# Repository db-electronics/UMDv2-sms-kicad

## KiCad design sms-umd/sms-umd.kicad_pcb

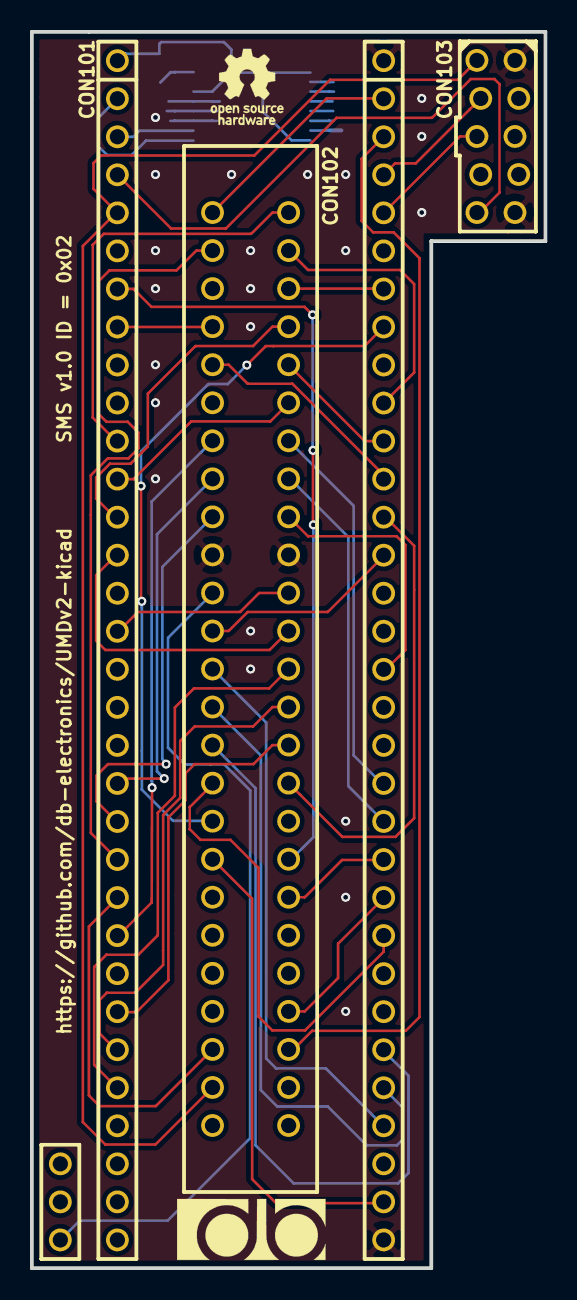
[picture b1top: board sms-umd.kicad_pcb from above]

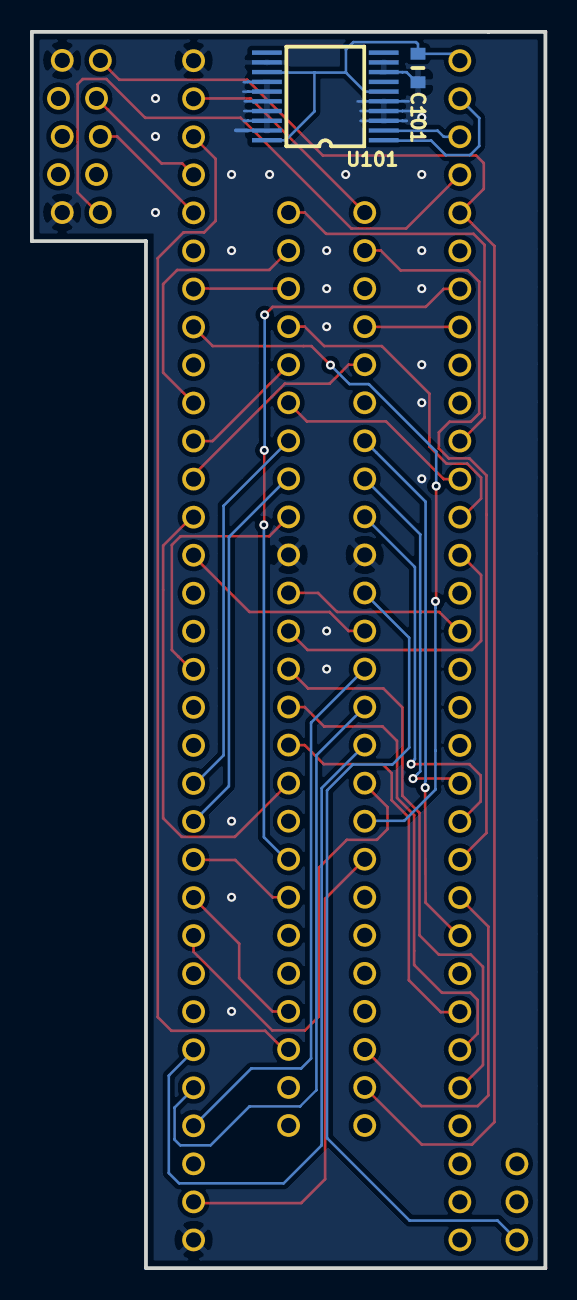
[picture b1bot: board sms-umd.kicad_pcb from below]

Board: 2 copper layers, 34.3 x 82.5 mm, 5 parts (2 on the bottom side), 43 nets.

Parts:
C101: 0.1uF/50V; 0603
CON101: UMDv2-CONN; UMD-CONN-DIP64
CON102: SMS-CONN
CON103: JTAG-2X5-HDR; HDR2X5-JTAG
U101: MCP23008T-E_SS; SSOP-20

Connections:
+3V3: C101.1, CON101.1, U101.6, U101.13, U101.20
/5V_0: CON101.63, CON102.1
/5V_1: CON101.34, CON102.35
/A0: CON101.36, CON102.25
/A1: CON101.28, CON102.26
/A2: CON101.37, CON102.27
/A3: CON101.27, CON102.28
/A4: CON101.38, CON102.29
/A5: CON101.26, CON102.30
/A6: CON101.41, CON102.31
/A7: CON101.52, CON102.32
/A8: CON101.13, CON102.8
/A9: CON101.53, CON102.9
/A10: CON101.12, CON102.12
/A11: CON101.54, CON102.10
/A12: CON101.57, CON102.33
/A13: CON101.8, CON102.7
/A14: CON101.58, CON102.6
/A15: CON101.7, CON102.36
/D0: CON101.14, CON102.24
/D1: CON101.51, CON102.23
/D2: CON101.16, CON102.22
/D3: CON101.48, CON102.18
/D4: CON101.21, CON102.17
/D5: CON101.44, CON102.16
/D6: CON101.20, CON102.15
/D7: CON101.45, CON102.14
/SCL: CON101.2, U101.1
/SDA: CON101.3, U101.2
/TCK: CON101.5, CON102.47, CON103.1
/TDI: CON101.4, CON103.9
/TDO: CON101.61, CON103.3
/TMS: CON101.60, CON103.5
/~BUSACK~: CON101.23, CON102.45
/~BUSREQ~: CON101.42, CON102.44
/~CART~: CON101.67, CON102.21
/~CE~: CON101.24, CON102.13
/~IORQ~: CON101.43, CON102.38
/~MREQ~: CON101.22, CON102.3
/~RD~: CON101.55, CON102.4
/~RST~: CON101.62, CON102.46
/~WR~: CON101.11, CON102.2
GND: C101.2, CON101.33, CON101.64, CON102.19, CON102.20, CON103.2, CON103.10, U101.3, U101.4, U101.5, U101.8, U101.9, U101.12, U101.14, U101.15, U101.16, U101.17, U101.18, U101.19

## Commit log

2020-03-06 initial files commit
2020-03-07 I dunno
2020-03-11 started laying out and routing the PCB
2020-03-14 prelim routing completed
2020-03-21 added OSHWA marking for v1.0 release
